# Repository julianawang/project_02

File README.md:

# project_02 - PCB Board Design for LED Music Visualizer
A PCB board design based off of Project 01, a board that allows an LED strip to react to a music recording:

https://github.com/julianawang/project_01

Link to Project 01 Hackster.io page with build and operation instructions:

https://www.hackster.io/juliana-wang/pocketbeagle-led-music-visualizer-3e6c7c

## Repository Contents
*EAGLE* - music_visualizer schematic and board. Also contains the library of components used in the design (includes a USB hub and a wire connector)

*MFG* - Gerber files, drill file, and BOM generated by the EAGLE Cam Processor; files needed for manufacturing from PCB producers such as Macrofab

*docs* - proposal powerpoint, Gerber file visualizations, BOM, and schematic PDF

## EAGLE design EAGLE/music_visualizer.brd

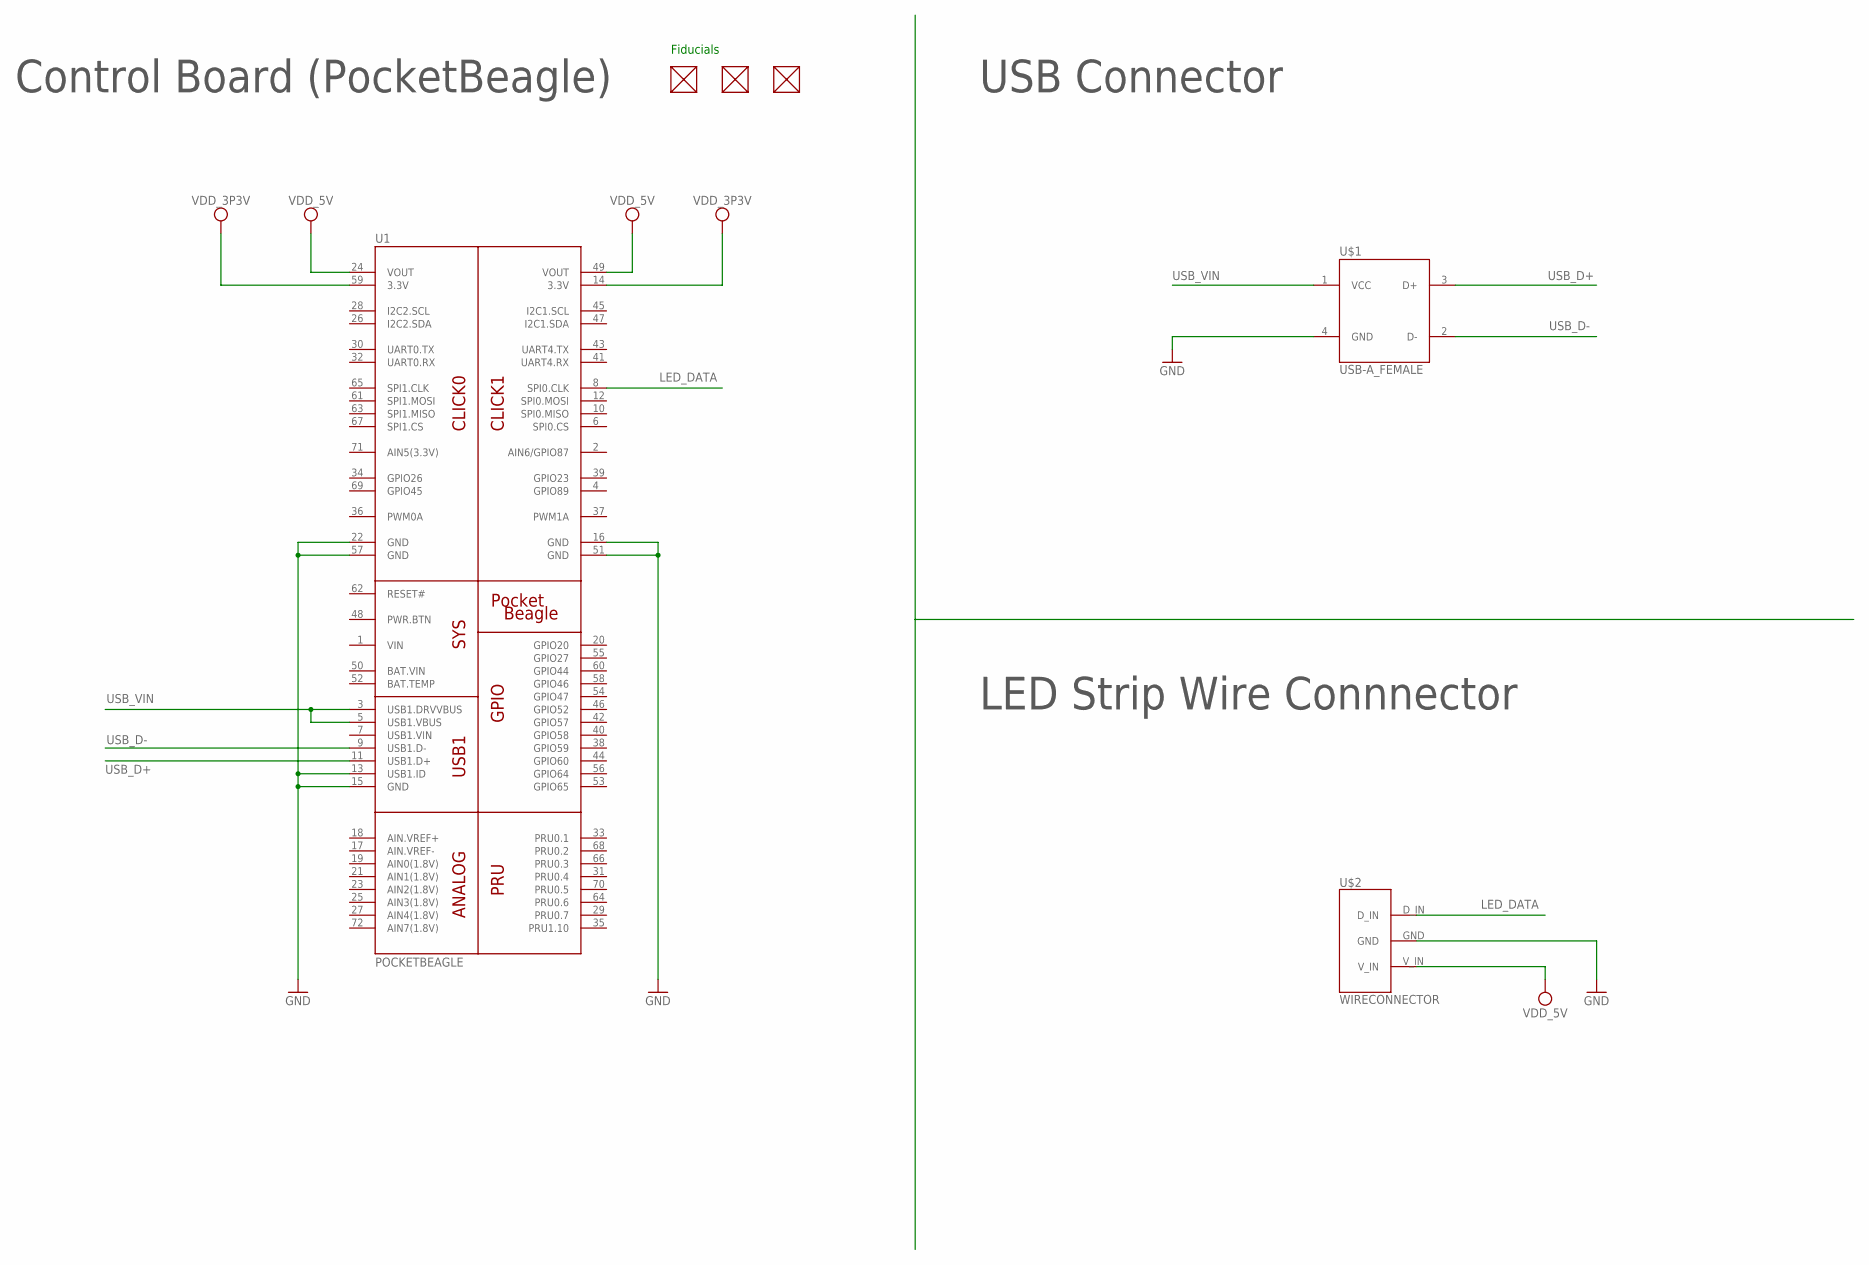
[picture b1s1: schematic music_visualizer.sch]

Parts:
FUD1, FUD2, FUD3: FIDUCIAL; FIDUCIAL_40MIL
U1: POCKETBEAGLE
U$1: USB-A_FEMALE
U$2: WIRECONNECTOR

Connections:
BAT.VIN: U1.50 (BAT.VIN)
GND: U1.13 (USB1.ID), U1.15 (GND), U1.16 (GND), U1.22 (GND), U1.51 (GND), U1.57 (GND), U$1.4 (GND), U$2.GND
LED_DATA: U1.8 (SPI0.CLK), U$2.D_IN
USB_D+: U1.11 (USB1.D+), U$1.3 (D+)
USB_D-: U1.9 (USB1.D-), U$1.2 (D-)
USB_VIN: U1.3 (USB1.DRVVBUS), U1.5 (USB1.VBUS), U$1.1 (VCC)
VDD_3P3V: U1.14 (3.3V), U1.59 (3.3V)
VDD_5V: U1.24 (VOUT), U1.49 (VOUT), U$2.V_IN
VIN: U1.1 (VIN)

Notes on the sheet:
USB Connector
LED Strip Wire Connnector
Control Board (PocketBeagle)
Fiducials

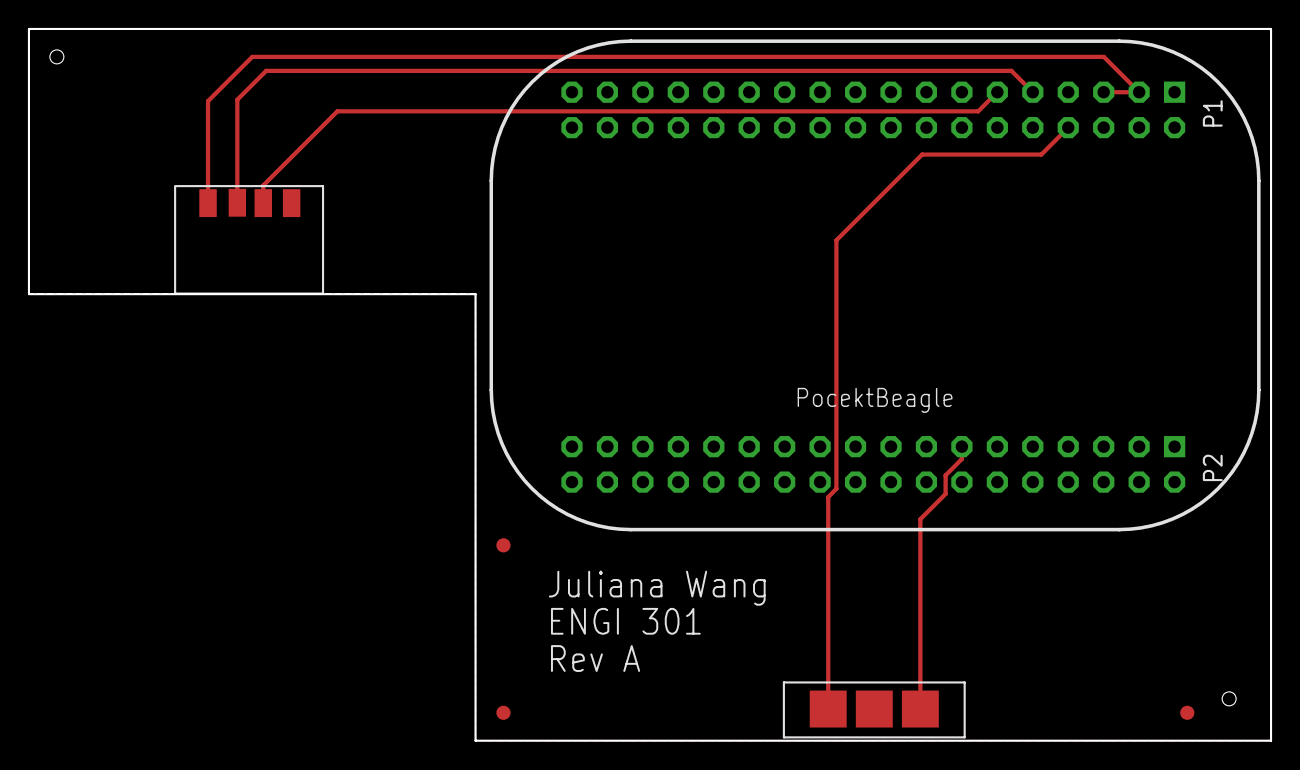
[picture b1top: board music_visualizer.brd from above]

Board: 2 copper layers, 89.0 x 51.0 mm, 6 parts (0 on the bottom side), 7 nets.

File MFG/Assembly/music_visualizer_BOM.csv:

Designator,Value,Package,Qty,Manufacturer,Description
FUD1-FUD3,FIDUCIAL,FIDUCIAL_40MIL,3,n/a,Fiducials
U1,POCKETBEAGLE,POCKETBEAGLE,1,BeagleBoard,PocketBeagle
U$1,USB-A_FEMALE,USB-A_FEMALE,1,Würth Elektronik,USB Type A Hub
U$2,WIRECONNECTOR,WIRECONNECTOR,1,AVX,LED Wire Strip Connector
,,,,,

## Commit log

2019-11-27 Create ignore
2021-03-26 Update README.md
    Fixed a typo
